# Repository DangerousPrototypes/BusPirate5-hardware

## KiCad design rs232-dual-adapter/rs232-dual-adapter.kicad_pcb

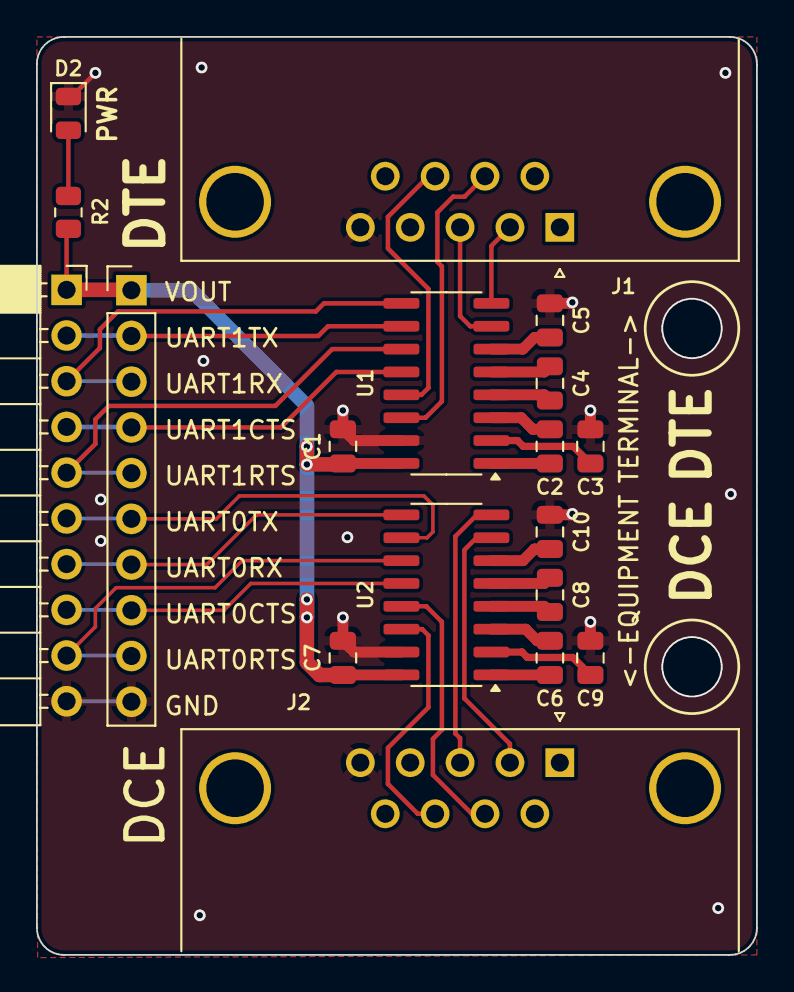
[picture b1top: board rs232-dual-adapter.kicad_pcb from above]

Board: 2 copper layers, 40.0 x 51.0 mm, 18 parts (0 on the bottom side), 31 nets.

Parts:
C1, C2, C6, C7: 0.1uF; C_0805_2012Metric
C3, C4, C5, C8, C9, C10: 0.47uF; C_0805_2012Metric
D2: LED; LED_0805_2012Metric
J1: COM1; DSUB-9_Male_Horizontal_P2.77x2.84mm_EdgePinOffset7.70mm_Hou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
J2: COM2; DSUB-9_Female_Horizontal_P2.77x2.84mm_EdgePinOffset7.70mm_H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
J3: Conn_01x10; PinHeader_1x10_P2.54mm_Vertical
J4: Conn_01x10; PinSocket_1x10_P2.54mm_Horizontal
R2: 2K; R_0805_2012Metric
U1, U2: MAX3232; SOP-16_3.9x9.9mm_P1.27mm

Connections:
/DCE_CTS: J2.8, U2.14 (T1OUT)
/DCE_RTS: J2.7, U2.13 (R1IN)
/DCE_RXD: J2.2, U2.7 (T2OUT)
/DCE_TXD: J2.3, U2.8 (R2IN)
/DTE_CTS: J1.8, U1.13 (R1IN)
/DTE_RTS: J1.7, U1.14 (T1OUT)
/DTE_RXD: J1.2, U1.8 (R2IN)
/DTE_TXD: J1.3, U1.7 (T2OUT)
GND: C1.2, C3.2, C5.2, C7.2, C9.2, C10.2, D2.1 (K), J1.5, J2.5, J3.10, J4.10, U1.15 (GND), U2.15 (GND)
unnamed: D2.2 (A), R2.2
unnamed: C2.1, U1.1 (C1+)
unnamed: C2.2, U1.3 (C1-)
unnamed: C4.1, U1.4 (C2+)
unnamed: C4.2, U1.5 (C2-)
unnamed: C3.1, U1.2 (VS+)
unnamed: C5.1, U1.6 (VS-)
unnamed: C6.1, U2.1 (C1+)
unnamed: C6.2, U2.3 (C1-)
unnamed: C8.1, U2.4 (C2+)
unnamed: C8.2, U2.5 (C2-)
unnamed: C9.1, U2.2 (VS+)
unnamed: C10.1, U2.6 (VS-)
UART0CTS: J3.8, J4.8, U2.12 (R1OUT)
UART0RTS: J3.9, J4.9, U2.11 (T1IN)
UART0RX: J3.7, J4.7, U2.9 (R2OUT)
UART0TX: J3.6, J4.6, U2.10 (T2IN)
UART1CTS: J3.4, J4.4, U1.12 (R1OUT)
UART1RTS: J3.5, J4.5, U1.11 (T1IN)
UART1RX: J3.3, J4.3, U1.9 (R2OUT)
UART1TX: J3.2, J4.2, U1.10 (T2IN)
VOUT: C1.1, C7.1, J3.1, J4.1, R2.1, U1.16 (VCC), U2.16 (VCC)

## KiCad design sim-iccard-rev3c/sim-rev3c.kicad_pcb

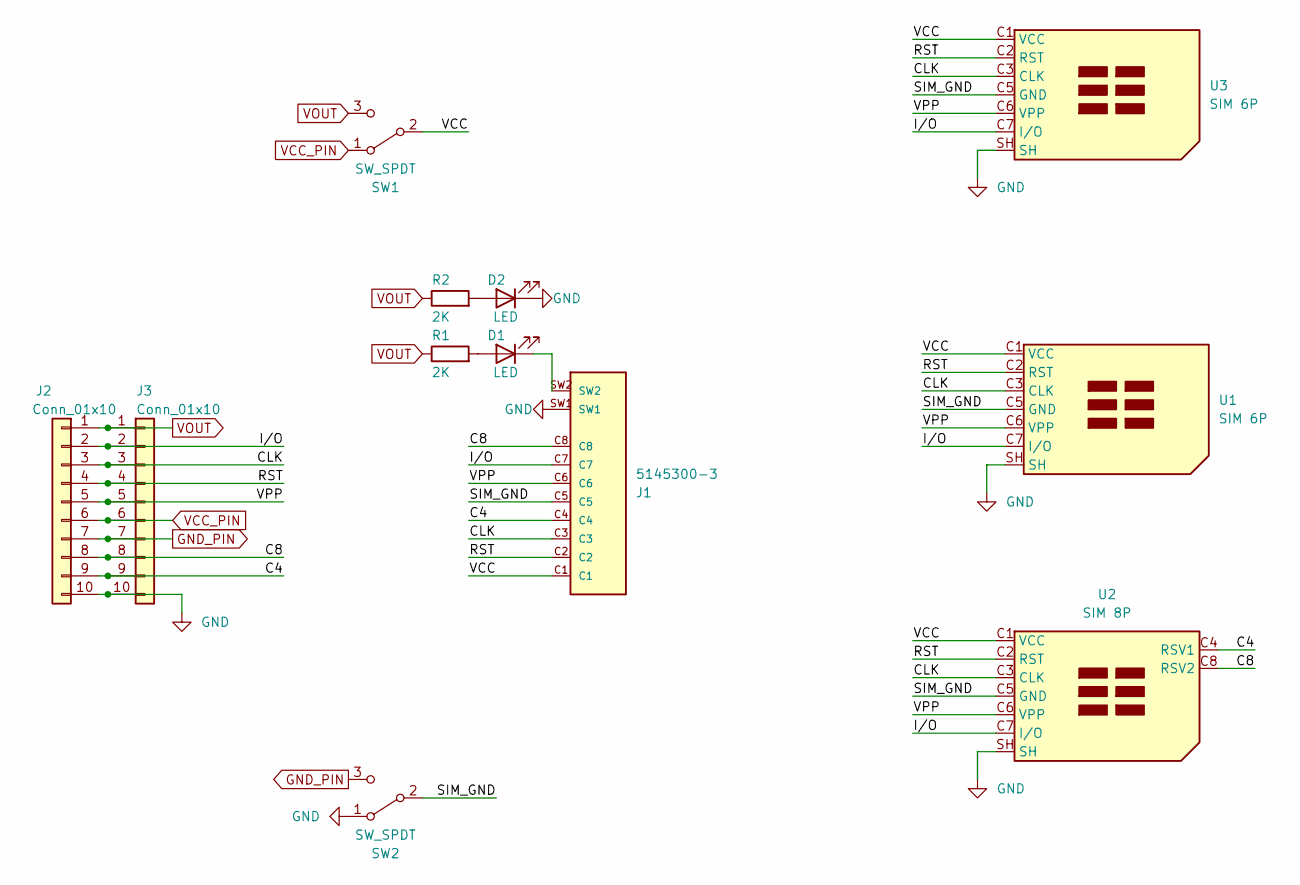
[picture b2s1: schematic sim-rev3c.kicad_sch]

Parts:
D1, D2: LED; LED_0805_2012Metric
J1: 5145300-3; TE_5145300-3; PARTREV C3
J2: Conn_01x10; PinSocket_1x10_P2.54mm_Horizontal
J3: Conn_01x10; PinHeader_1x10_P2.54mm_Vertical
R1, R2: 2K; R_0805_2012Metric
SW1, SW2: SW_SPDT; SW_SPDT_PCM12
U1: SIM 6P; DGLZ-SIM-0004
U2: SIM 8P; SIM-0030
U3: SIM 6P; SIM-0036

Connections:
/C4: J1.C4, J2.9, J3.9, U2.C4 (RSV1)
/C8: J1.C8, J2.8, J3.8, U2.C8 (RSV2)
/CLK: J1.C3, J2.3, J3.3, U1.C3 (CLK), U2.C3 (CLK), U3.C3 (CLK)
/I/O: J1.C7, J2.2, J3.2, U1.C7 (I/O), U2.C7 (I/O), U3.C7 (I/O)
/RST: J1.C2, J2.4, J3.4, U1.C2 (RST), U2.C2 (RST), U3.C2 (RST)
/SIM_GND: J1.C5, SW2.2 (B), U1.C5 (GND), U2.C5 (GND), U3.C5 (GND)
/VCC: J1.C1, SW1.2 (B), U1.C1 (VCC), U2.C1 (VCC), U3.C1 (VCC)
/VPP: J1.C6, J2.5, J3.5, U1.C6 (VPP), U2.C6 (VPP), U3.C6 (VPP)
GND: D2.1 (K), J1.SW1, J2.10, J3.10, SW2.1 (A), U1.SH, U2.SH, U3.SH
GND_PIN: J2.7, J3.7, SW2.3 (C)
unnamed: D1.2 (A), R1.2
unnamed: D1.1 (K), J1.SW2
unnamed: D2.2 (A), R2.2
VCC_PIN: J2.6, J3.6, SW1.1 (A)
VOUT: J2.1, J3.1, R1.1, R2.1, SW1.3 (C)

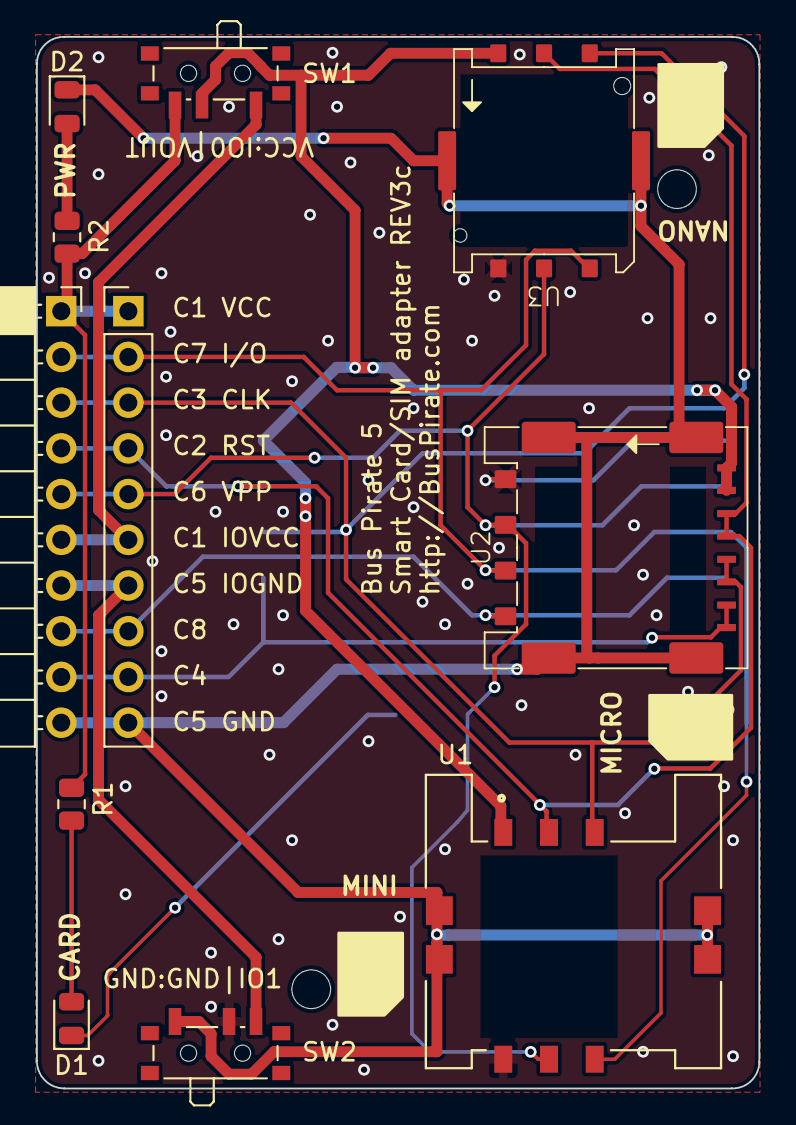
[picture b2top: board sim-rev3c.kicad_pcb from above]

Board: 2 copper layers, 40.1 x 58.4 mm, 12 parts (1 on the bottom side), 15 nets.

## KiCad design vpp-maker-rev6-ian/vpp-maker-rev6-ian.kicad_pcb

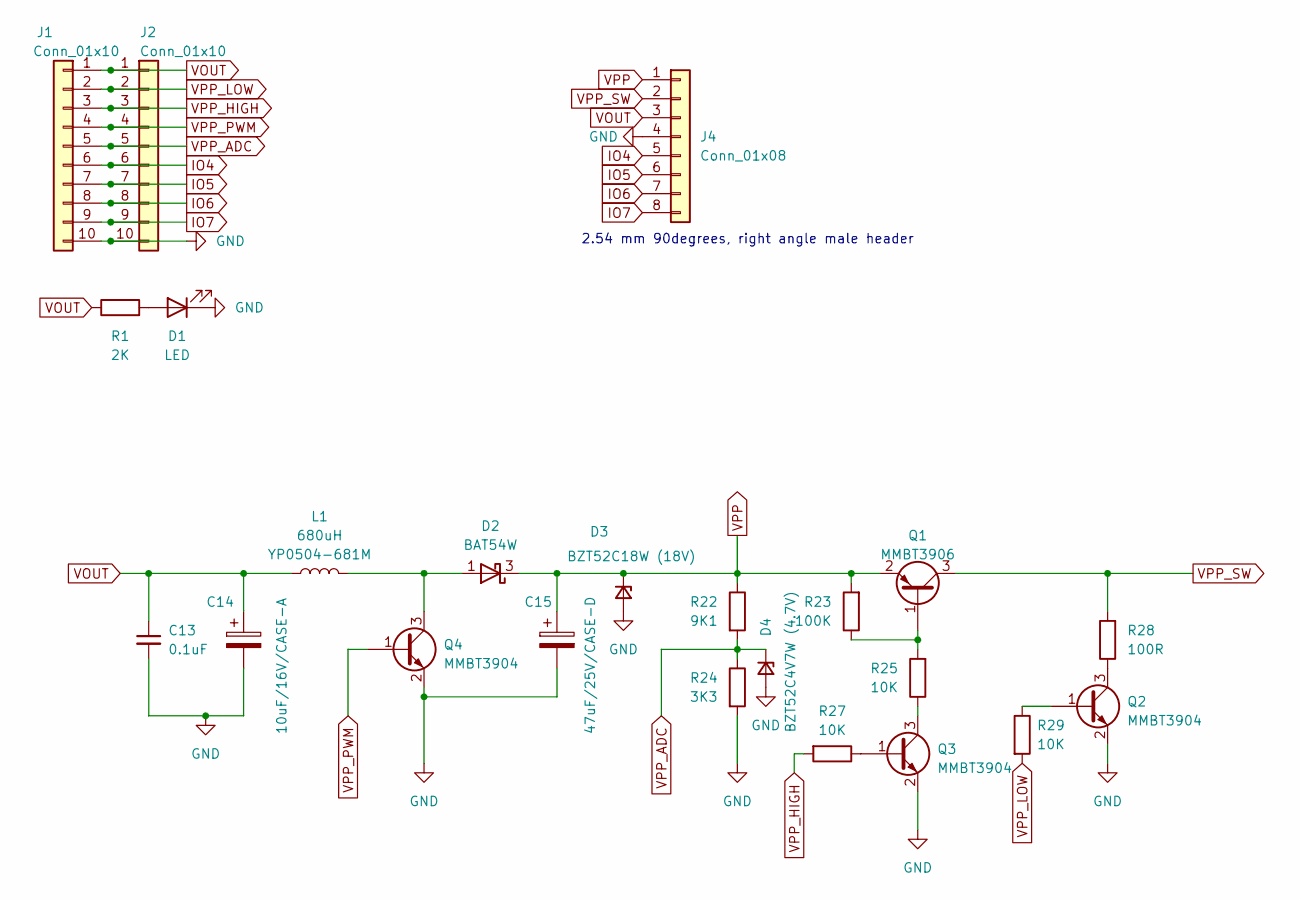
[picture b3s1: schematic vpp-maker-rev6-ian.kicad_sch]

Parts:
C13: 0.1uF; C_0805_2012Metric_Pad1.18x1.45mm_HandSolder
C14: 10uF/16V/CASE-A; CP_EIA-3216-18_Kemet-A
C15: 47uF/25V/CASE-D; CP_EIA-7343-31_Kemet-D
D1: LED; LED_0805_2012Metric
D2: BAT54W; SOT-23
D3: BZT52C18W (18V); D_SOD-123
D4: BZT52C4V7W (4.7V); D_SOD-123
J1: Conn_01x10; PinSocket_1x10_P2.54mm_Horizontal
J2: Conn_01x10; PinHeader_1x10_P2.54mm_Vertical
J4: Conn_01x08; PinHeader_1x08_P2.54mm_Horizontal
L1: 680uH; L_YP0504; MPN YP0504-681M
Q1: MMBT3906; SOT-23
Q2, Q3, Q4: MMBT3904; SOT-23
R1: 2K; R_0805_2012Metric
R22: 9K1; R_0805_2012Metric
R23: 100K; R_0805_2012Metric
R24: 3K3; R_0805_2012Metric
R25, R27, R29: 10K; R_0805_2012Metric
R28: 100R; R_0805_2012Metric

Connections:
GND: C13.2, C14.2, C15.2, D1.1 (K), D3.2 (A), D4.2 (A), J1.10, J2.10, J4.4, Q2.2 (E), Q3.2 (E), Q4.2 (E), R24.2
IO4: J1.6, J2.6, J4.5
IO5: J1.7, J2.7, J4.6
IO6: J1.8, J2.8, J4.7
IO7: J1.9, J2.9, J4.8
unnamed: D1.2 (A), R1.2
unnamed: D2.1 (A), L1.2, Q4.3 (C)
unnamed: Q1.1 (B), R23.1, R25.2
unnamed: Q2.1 (B), R29.1
unnamed: Q2.3 (C), R28.1
unnamed: Q3.1 (B), R27.1
unnamed: Q3.3 (C), R25.1
VOUT: C13.1, C14.1, J1.1, J2.1, J4.3, L1.1, R1.1
VPP: C15.1, D2.3 (K), D3.1 (K), J4.1, Q1.2 (E), R22.1, R23.2
VPP_ADC: D4.1 (K), J1.5, J2.5, R22.2, R24.1
VPP_HIGH: J1.3, J2.3, R27.2
VPP_LOW: J1.2, J2.2, R29.2
VPP_PWM: J1.4, J2.4, Q4.1 (B)
VPP_SW: J4.2, Q1.3 (C), R28.2

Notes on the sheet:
2.54 mm 90degrees, right angle male header

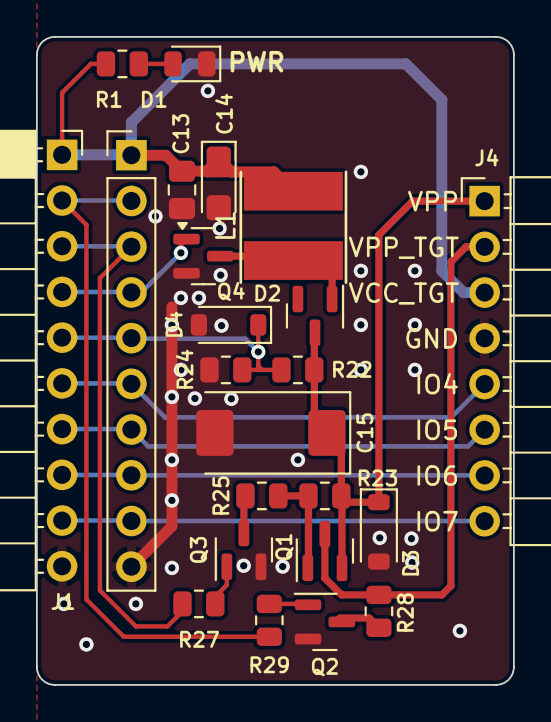
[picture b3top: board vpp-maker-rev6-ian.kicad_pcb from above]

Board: 2 copper layers, 26.5 x 36.0 mm, 23 parts (0 on the bottom side), 19 nets.

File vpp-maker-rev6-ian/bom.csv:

"Reference","Value","Datasheet","Footprint","Qty","DNP"
"C13","0.1uF","~","Capacitor_SMD:C_0805_2012Metric_Pad1.18x1.45mm_HandSolder","1",""
"C14","10uF/16V/CASE-A","~","Capacitor_Tantalum_SMD:CP_EIA-3216-18_Kemet-A","1",""
"C15","47uF/25V/CASE-D","~","Capacitor_Tantalum_SMD:CP_EIA-7343-31_Kemet-D","1",""
"D1","LED","~","LED_SMD:LED_0805_2012Metric","1",""
"D2","BAT54W","https://assets.nexperia.com/documents/data-sheet/BAT54W_SER.pdf","Package_TO_SOT_SMD:SOT-23","1",""
"J1,J2","Conn_01x10","~","-- mixed values --","2",""
"J4","Conn_01x08","~","Connector_PinHeader_2.54mm:PinHeader_1x08_P2.54mm_Horizontal","1",""
"L1","680uH","~","Library:IND-SMD_L5.8-W5.2","1",""
"Q1","MMBT3906","https://www.onsemi.com/pub/Collateral/2N3906-D.PDF","Package_TO_SOT_SMD:SOT-23","1",""
"Q2,Q3,Q4","MMBT3904","https://www.onsemi.com/pub/Collateral/2N3903-D.PDF","Package_TO_SOT_SMD:SOT-23","3",""
"R1","2K","~","Resistor_SMD:R_0805_2012Metric","1",""
"R22","4.7K??","~","Resistor_SMD:R_0805_2012Metric","1",""
"R23","100K","~","Resistor_SMD:R_0805_2012Metric","1",""
"R24","2.7K","~","Resistor_SMD:R_0805_2012Metric","1",""
"R25,R27,R29","10K","~","Resistor_SMD:R_0805_2012Metric","3",""
"R28","100R","~","Resistor_SMD:R_0805_2012Metric","1",""
